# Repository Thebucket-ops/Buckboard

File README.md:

# ***THE BUCKBOARD***

The buckboard is a 60% keyboard with a integrated joystick that simulates the arrow keys and a tiny oled screen.
This project uses a raspberry pi pico as microcontroller.
Altough the project offers a pcb for the keyboard, the case is made for hand wired keyboard and it should be used just for reference on how to wire up everything (still you could use the pcb, you just need to make some adjustments to the bottom part of the case)

## **CASE**

the case 3d files can be found in /case

## **SCHEMATIC**

This is the schematich for the wiring of the keyboard, each key has its own key written down for ease of use

Each key has to be placed accordingly to how its shown below, the pcb layout is also helpful for wiring so look at it while you wire the keyboard

THIS IS A WIRED KEYBOARD, THE PCB, ALTOUGH PROBABLY WORKING, IS JUST FOR REFERENCE IN WIRING

## **WIRING**

Here's a schematic on the wiring of the keyboard, the points with the pin number are to be soldered to the indicated pin on the number

here are also the pins for all the non-key related connections:

 **rotary encoder**:
 - A -> GP14
 - B -> GP13

 **OLED display**:
 - GND -> GROUND
 - VCC -> 3.3V
 - SCL -> GP17
 - SDA -> GP16

 **JOYSTICK MODULE**:
 - GND -> GROUND
 - 5V/3.3V -> 3.3V
 - VRx -> GP27
 - VRy -> GP28
 - SW -> GND

## **FIRMWARE**

The firmware for the board is made in qmk, the keymap offered has the italian layout.
All files can be found on /firmware.
To flash the firmware simply turn on the devboard on bootloader mode and drag the uf2 file in the devboard.

## **BOM**

  The build requires:  
 - 1 pi pico (~7$/pcs [here](https://www.kubii.com/it/microcontrollori/3205-1639-raspberry-pi-pico-w-h-wh-3272496311589.html#/versione_pico-pico))
 - 1 rotary encoder (~15$/10pcs [here](https://www.amazon.it/RUNCCI-YUN-Rotativo-Potenziometro-Digitale-Interruttore/dp/B09SG3HF9N?dib=eyJ2IjoiMSJ9.F8wSD_ClX5zz0PV7IOKvMkRhgyj-cGrY_61fAiASZ94c_mqYwGcYO2LfgHDMmtkLLSino1Pd-_Z8fvpDhx8DIvmlWJccgXqmOFTzvwe1BLPanCgETyudOtUZT9Ufk_3F3Gbc0jFqR6dC4F8MQeamH-wypuVv5iJ48G5n8PrqyaYo7Gsi5FyNlbMGxPjJw6Yv8BhH01mSLIdqSywhAVNpqFnVbQmpprpa9KXmNVoyD8AuH2dO-ndtwUD7AGoTH5E1jhLOjCudrsIiiV8hci9BpDOvhlL3qAmJGjfxH4KTrhQ.eGlkaoZ4o36PyYWL80J3xJWT7rkP3XtXI0fsI0ih9ww&dib_tag=se&keywords=rotary+encoder&qid=1793640223&sr=8-4))
 - 1 joystick moudule (~10$/5pcs [here](https://www.amazon.it/ARCELI-Joystick-Breakout-Module-Arduino/dp/B077Z8QN3S?__mk_it_IT=%C3%85M%C3%85%C5%BD%C3%95%C3%91&crid=3DF8HYTAZMGI1&dib=eyJ2IjoiMSJ9.azcL_6pR9k-VQV-Bp9yBl-ovBqnUR6SjUehkSwaS5Wh2XCvc09OWHMWm41YyFK0PxCOkPQs40QXJPQhbPXYBKEpltBGW_IxIbLmfVi0qSEZw9uFkzg87gOWdravNtxWfebBmtJJjYdWhUvGoGDaQwbiKyFJjyrHCQgyBkecfKQSXlLZfLwYitYo09t7exWX6K8jyDtWcrnj2amiFMB4PMWpjNxR8lnZ5FUU6e6TvTZHMNT-gFap7kG7x7RUsfuPfS4JF8etH_q-v7D0ia59vx2_1AKPquWSYkonLvUhfjZo.Th0ATBVvj1aCIP76Lc_8X88_u4u22PmVYsjqk2jAaZY&dib_tag=se&keywords=joystick+module&qid=1793640403&sprefix=joystick+module%2Caps%2C135&sr=8-4) )
 - 77 keyswitches (~25$/150pcs [here](https://www.amazon.it/gp/product/B0GS645MLG?smid=A227R4NKW6D6GV&psc=1))
 - 78 diodes 1N914 (~15$/100pcs [here](https://www.amazon.it/ALLECIN-1N914-Commutazione-Velocit%C3%A0-200Milliampere/dp/B0CKRKW4HL?__mk_it_IT=%C3%85M%C3%85%C5%BD%C3%95%C3%91&crid=2HW74BA9NU1JU&dib=eyJ2IjoiMSJ9.U0E1T2Xju4EQatSApF4Tuzw-g1WjekXKZoI2FDeSbIZyvY9wVHP5yAVNW3Vx66AwNiZl7wO_9dRpSm7LXVrne4raZd2RQ9-a1_OBjpc72KTMBwaHVpICfEEdncFrTcBiSkuzopNsOFK5EJyBCrTf9OjJ9FrvfwXS666d1NP0-cxf1j37lhCjQzQHDN4vBf_z6tag3rAQaCj6ukxTrlu2u9d0vHg2CzgHsseIyi0e8xsktVY8lT55k3Io6-GlEya16wVekWTCXIJBUyhdD_XkfOiAB7swWxvqeQqY9CAFrlo.hJIcRd5SOuYRWmprUVa64lyLVXWE4hw9tTyIQ5iQS_o&dib_tag=se&keywords=1N914+Diodi&qid=1793639966&s=industrial&sprefix=1n914+diodi%2Cindustrial%2C113&sr=1-1))
 - 1 0.91" oled screen (~17$/3pcs [here](https://www.amazon.it/APKLVSR-display-visualizzazione-Arduino-microcontrollori/dp/B0D2L1ZDWP?__mk_it_IT=%C3%85M%C3%85%C5%BD%C3%95%C3%91&crid=1I0L3VM7VLJUO&dib=eyJ2IjoiMSJ9.IXiposGMPwzMW0L9MnGaq9dgOQjG1XXvP3NgpOOnqSB7DPO5px14HgRE8cgssMzXsi9u6_GTI-vA6X8fb1JW-Zl-8V7hUkKJ1Z0tshoToXaaWXiQBs7qBp4dhLLViAcFUzTobb2ZESK0J-o3noKHusroRZcCWeoEo0rMvEAoog19ZfOoPaCfgOYXG4JijA4dPRZKrdMk-b0gpNwjDoFqHeBUiOdDUzaFT5iyqetnoXpY8Hqazzzcr5Gcd7adHxb1m3fpojiS9mmD4eQ_ZmFuV7_NsCmSS6t_1DXEQXrvp90.dQGyT7EEeWLV01y9welVgTHb6BP5IXY4zm3mwAeLQvw&dib_tag=se&keywords=0.91%22+oled+screen&qid=1793640685&sprefix=0.91+oled+screen%C3%B9%2Caps%2C131&sr=8-1))
 - wire for wiring (~12$/280m of wire [here](https://www.amazon.it/gp/product/B07KB3XVTB?smid=A1XDN6LSMACAXM&psc=1))
 - keycaps (~26$ [here](https://www.amazon.it/gp/product/B0B4JV49DG?smid=A11IL2PNWYJU7H&psc=1))
 Prices may vary based on your region

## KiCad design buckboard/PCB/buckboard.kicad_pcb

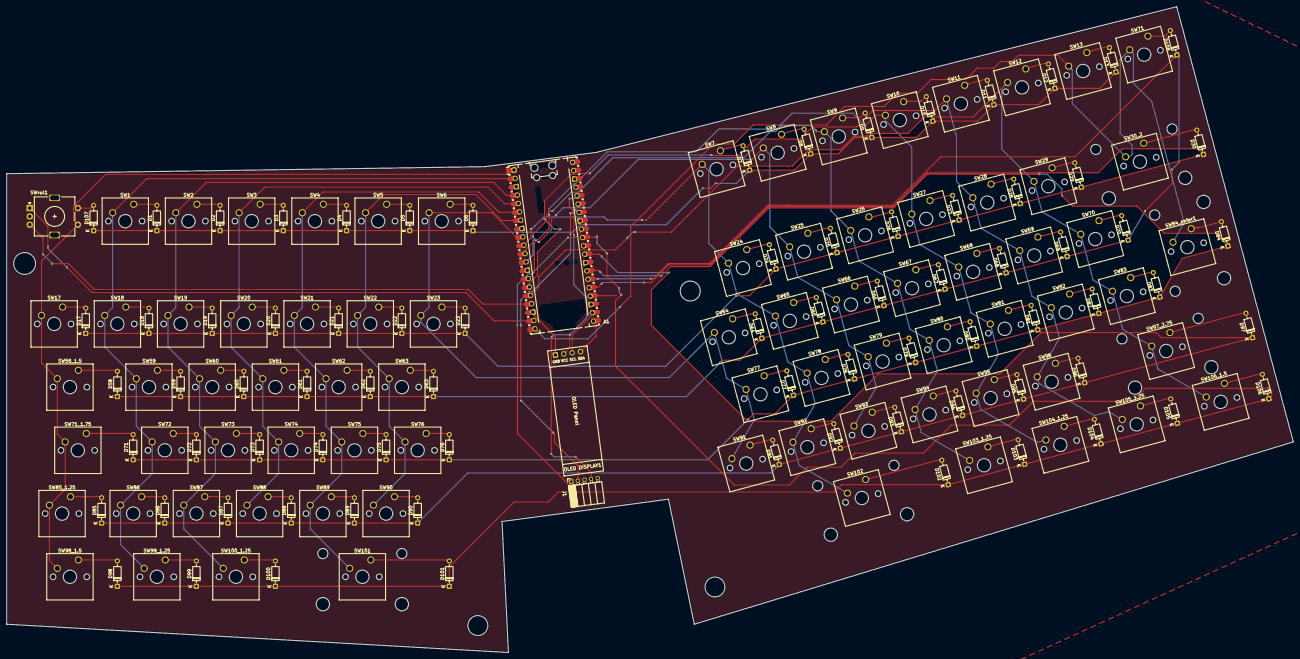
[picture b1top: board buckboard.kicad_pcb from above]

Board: 2 copper layers, 387.6 x 194.6 mm, 159 parts (0 on the bottom side), 107 nets.

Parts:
A1: RaspberryPi_Pico; RaspberryPi_Pico_Common_Unspecified
D1, D2, D3, D4, D5, D6, D7, D8, D9, D10, D11, D12, D13, D17, D18, D19, D20, D21, D22, D23, D24, D25, D26, D27, D28, D29, D30, D58, D59, D60, D61, D62, D63, D64, D65, D66, D67, D68, D69, D70, D71, D72, D73, D74, D75, D76, D77, D78, D79, D80, D81, D82, D83, D84, D85, D86, D87, D88, D89, D90, D91, D92, D93, D94, D95, D96, D97, D98, D99, D100, D101, D102, D103, D104, D105, D106, D107, D108: 1N914; D_DO-35_SOD27_P7.62mm_Horizontal
J1: Conn_01x05; PinSocket_1x05_P2.00mm_Horizontal
OLED DISPLAY1: SSD1306-0.91-OLED-4pin-128x32
SW1, SW2, SW3, SW4, SW5, SW6, SW7, SW8, SW9, SW10, SW11, SW12, SW13, SW17, SW18, SW19, SW20, SW21, SW22, SW23, SW24, SW25, SW26, SW27, SW28, SW29, SW59, SW60, SW61, SW62, SW63, SW64, SW65, SW66, SW67, SW68, SW69, SW70, SW71, SW72, SW73, SW74, SW75, SW76, SW77, SW78, SW79, SW80, SW81, SW82, SW83, SW86, SW87, SW88, SW89, SW90, SW91, SW92, SW93, SW94, SW95, SW96: SW_Push; SW_Cherry_MX_1.00u_PCB
SW30_2: SW_Push; SW_Cherry_MX_2.00u_PCB
SW58_1.5, SW98_1.5, SW106_1.5: SW_Push; SW_Cherry_MX_1.50u_PCB
SW71_1.75: SW_Push; SW_Cherry_MX_1.75u_PCB
SW84_enter1: SW_Push; SW_Cherry_MX_ISOEnter_PCB
SW85_1.25, SW99_1.25, SW100_1.25, SW103_1.25, SW104_1.25, SW105_1.25: SW_Push; SW_Cherry_MX_1.25u_PCB
SW97_2.75, SW101, SW102: SW_Push; SW_Cherry_MX_2.75u_PCB
SWvol1: RotaryEncoder_Switch; RotaryEncoder_Alps_EC11E-Switch_Vertical_H20mm

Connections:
+3.3V: A1.36 (3V3), J1.4, OLED DISPLAY1.2 (SCL_2)
EC11A: A1.19 (GPIO14), SWvol1.A
EC11B: A1.17 (GPIO13), SWvol1.B
EC11SWA: D107.2 (A), SWvol1.S2
EC11SWB: A1.1 (GPIO0), SW17.2, SW58_1.5.2, SW71_1.75.2, SW85_1.25.2, SW98_1.5.2, SWvol1.S1
GND: A1.3 (GND), A1.8 (GND), A1.13 (GND), A1.18 (GND), A1.23 (GND), A1.28 (GND), A1.38 (GND), J1.5, OLED DISPLAY1.1 (SDA_1), SWvol1.C
JSW: A1.37 (3V3_EN), J1.1
unnamed: D1.2 (A), SW1.1
unnamed: D2.2 (A), SW2.1
unnamed: D3.2 (A), SW3.1
unnamed: D4.2 (A), SW4.1
unnamed: D5.2 (A), SW5.1
unnamed: D6.2 (A), SW6.1
unnamed: D7.2 (A), SW7.1
unnamed: D8.2 (A), SW8.1
unnamed: D9.2 (A), SW9.1
unnamed: D10.2 (A), SW10.1
unnamed: D11.2 (A), SW11.1
unnamed: D12.2 (A), SW12.1
unnamed: D13.2 (A), SW13.1
unnamed: D17.2 (A), SW17.1
unnamed: D18.2 (A), SW18.1
unnamed: D19.2 (A), SW19.1
unnamed: D20.2 (A), SW20.1
unnamed: D21.2 (A), SW21.1
unnamed: D22.2 (A), SW22.1
unnamed: D23.2 (A), SW23.1
unnamed: D24.2 (A), SW24.1
unnamed: D25.2 (A), SW25.1
unnamed: D26.2 (A), SW26.1
unnamed: D27.2 (A), SW27.1
unnamed: D28.2 (A), SW28.1
unnamed: D29.2 (A), SW29.1
unnamed: D30.2 (A), SW30_2.1
unnamed: D58.2 (A), SW58_1.5.1
unnamed: D59.2 (A), SW59.1
unnamed: D60.2 (A), SW60.1
unnamed: D61.2 (A), SW61.1
unnamed: D62.2 (A), SW62.1
unnamed: D63.2 (A), SW63.1
unnamed: D64.2 (A), SW64.1
unnamed: D65.2 (A), SW65.1
unnamed: D66.2 (A), SW66.1
unnamed: D67.2 (A), SW67.1
unnamed: D68.2 (A), SW68.1
unnamed: D69.2 (A), SW69.1
unnamed: D70.2 (A), SW70.1
unnamed: D71.2 (A), SW71_1.75.1
unnamed: D72.2 (A), SW72.1
unnamed: D73.2 (A), SW73.1
unnamed: D74.2 (A), SW74.1
unnamed: D75.2 (A), SW75.1
unnamed: D76.2 (A), SW76.1
unnamed: D77.2 (A), SW77.1
unnamed: D78.2 (A), SW78.1
unnamed: D79.2 (A), SW79.1
unnamed: D80.2 (A), SW80.1
unnamed: D81.2 (A), SW81.1
unnamed: D82.2 (A), SW82.1
unnamed: D83.2 (A), SW83.1
unnamed: D84.2 (A), SW84_enter1.1
unnamed: D85.2 (A), SW85_1.25.1
unnamed: D86.2 (A), SW86.1
unnamed: D87.2 (A), SW87.1
unnamed: D88.2 (A), SW88.1
unnamed: D89.2 (A), SW89.1
unnamed: D90.2 (A), SW90.1
unnamed: D91.2 (A), SW91.1
unnamed: D92.2 (A), SW92.1
unnamed: D93.2 (A), SW93.1
unnamed: D94.2 (A), SW94.1
unnamed: D95.2 (A), SW95.1
unnamed: D96.2 (A), SW96.1
unnamed: D97.2 (A), SW97_2.75.1
unnamed: D98.2 (A), SW98_1.5.1
unnamed: D99.2 (A), SW99_1.25.1
unnamed: D100.2 (A), SW100_1.25.1
unnamed: D101.2 (A), SW101.1
unnamed: D102.2 (A), SW102.1
unnamed: D103.2 (A), SW103_1.25.1
unnamed: D104.2 (A), SW104_1.25.1
unnamed: D105.2 (A), SW105_1.25.1
unnamed: D106.2 (A), SW106_1.5.1
unnamed: D108.2 (A), SW71.1
SCL: A1.22 (GPIO17), OLED DISPLAY1.sc (VCC_3)
SDA: A1.21 (GPIO16), OLED DISPLAY1.s (GND_4)
VRx: A1.32 (GPIO27_ADC1), J1.3
VRy: A1.34 (GPIO28_ADC2), J1.2
col2: A1.2 (GPIO1), SW1.2, SW18.2, SW59.2, SW72.2, SW86.2, SW99_1.25.2
col3: A1.4 (GPIO2), SW2.2, SW19.2, SW60.2, SW73.2, SW87.2, SW100_1.25.2
col4: A1.5 (GPIO3), SW3.2, SW20.2, SW61.2, SW74.2, SW88.2
col5: A1.6 (GPIO4), SW4.2, SW21.2, SW62.2, SW75.2, SW89.2, SW101.2
col6: A1.7 (GPIO5), SW5.2, SW22.2, SW63.2, SW76.2, SW90.2
col7: A1.9 (GPIO6), SW6.2, SW23.2, SW64.2, SW77.2, SW91.2
col8: A1.10 (GPIO7), SW7.2, SW24.2, SW65.2, SW78.2, SW92.2, SW102.2
col9: A1.11 (GPIO8), SW8.2, SW25.2, SW66.2, SW79.2, SW93.2
col10: A1.12 (GPIO9), SW9.2, SW26.2, SW67.2, SW80.2, SW94.2, SW103_1.25.2
col11: A1.14 (GPIO10), SW10.2, SW27.2, SW68.2, SW81.2, SW95.2, SW104_1.25.2
col12: A1.15 (GPIO11), SW11.2, SW28.2, SW69.2, SW82.2, SW96.2, SW105_1.25.2
col13: A1.16 (GPIO12), SW12.2, SW29.2, SW70.2, SW83.2, SW97_2.75.2, SW106_1.5.2
col14: A1.20 (GPIO15), SW13.2, SW30_2.2, SW71.2, SW84_enter1.2
p19: A1.25 (GPIO19), D17.1 (K), D18.1 (K), D19.1 (K), D20.1 (K), D21.1 (K), D22.1 (K), D23.1 (K), D24.1 (K), D25.1 (K), D26.1 (K), D27.1 (K), D28.1 (K), D29.1 (K), D30.1 (K)
p20: A1.26 (GPIO20), D58.1 (K), D59.1 (K), D60.1 (K), D61.1 (K), D62.1 (K), D63.1 (K), D64.1 (K), D65.1 (K), D66.1 (K), D67.1 (K), D68.1 (K), D69.1 (K), D70.1 (K), D108.1 (K)
p21: A1.27 (GPIO21), D71.1 (K), D72.1 (K), D73.1 (K), D74.1 (K), D75.1 (K), D76.1 (K), D77.1 (K), D78.1 (K), D79.1 (K), D80.1 (K), D81.1 (K), D82.1 (K), D83.1 (K), D84.1 (K)
p22: A1.29 (GPIO22), D85.1 (K), D86.1 (K), D87.1 (K), D88.1 (K), D89.1 (K), D90.1 (K), D91.1 (K), D92.1 (K), D93.1 (K), D94.1 (K), D95.1 (K), D96.1 (K), D97.1 (K)
p26: A1.31 (GPIO26_ADC0), D98.1 (K), D99.1 (K), D100.1 (K), D101.1 (K), D102.1 (K), D103.1 (K), D104.1 (K), D105.1 (K), D106.1 (K)
row1: D1.1 (K), D2.1 (K), D3.1 (K), D4.1 (K), D5.1 (K), D6.1 (K), D7.1 (K), D8.1 (K), D9.1 (K), D10.1 (K), D11.1 (K), D12.1 (K), D13.1 (K), D107.1 (K)

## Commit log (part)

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2026-06-08 started pcb
2026-06-09 wiring
2026-06-28 organized pcb
    Man its a pain to organize all those switches and diodes one by one
